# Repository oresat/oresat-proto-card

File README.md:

# "oresat-proto-card"

This is the "prototype" card for OreSat, meant to pioneer future cards and test the backplane, and be an 
easy way to hack in functionality. NOT MEANT FOR FLIGHT.

## Features

- Populates the two 1.27 mm connectors from the backplane.
- Populates all three SMPM RF connectors from the backplane.
- Standard TPS63070-bsaed buck/boost SPS (Vin = 2.5 to 7 V, Vout = 3.3V)
- Has our standard/favorite STM32F042K6 microcontroller.
   - With SWD, UART (FTDI), and CAN (to the backplane).
- Has lots of breakouts, but DO NOT POPULATE THE 0.1 IN CONNECTORS, THEY'RE TOO TALL!!!

## Connector information

- Main 1.27 mm connector ("Center" connector)
   - Samtec TFM-120-01-L-D-RA
   - https://www.digikey.com/products/en?lang=en&site=US&keywords=TFM-120-01-L-D-RA
   - Drawing: http://suddendocs.samtec.com/prints/tfm-1xx-xx-xxx-d-xxx-mkt.pdf
   - Brochure: http://suddendocs.samtec.com/catalog_english/tfm.pdf
   - 3D CAD: https://www.samtec.com/partnumber/tfm-120-01-l-d-ra?vendor=digikey#technical
   - Notes: the -RE1 model is better because of the solder stakes, but the female connector doesn't fit! The stakes get in the way :(

- Auxiliary 1.27 mm ("alt-left" connector)
   - Samtec TFM-110-01-L-D-RA

- RF (70 cm, L band, S band) conenctors
   - Card
      - Molex 73300-0030 (possible replacement is 73300-0020 but it has full detent that we don't want)
      - SMPM Connector Plug, Male Pin 50 Ohm Board Edge, Cutout; Surface Mount Solder, smooth bore
      - Molex w/3D: https://www.molex.com/molex/products/datasheet.jsp?part=active/0733000030_RF_COAX_CONNECTORS.xml
   - Barrell (connects card to backplane)
      - Molex 73300-0220 (alt but slightly different lengths: -0223, -0228)
      - SMPM female to female barrel adapter 
      - RF Adapters - In Series SMPM JACK/JACK BULLET .21IN
      - Molex w/3D: https://www.molex.com/molex/products/datasheet.jsp?part=active/0733000220_RF_COAX_CONNECTORS.xml

## LICENSE

Copyright Portland State Aerospace Society 2018.

This documentation describes Open Hardware and is licensed under the CERN OHL v. 1.2.

You may redistribute and modify this documentation under the terms of the CERN OHL v.1.2. [http://ohwr.org/cernohl](http://ohwr.org/cernohl). This documentation is distributed WITHOUT ANY EXPRESS OR IMPLIED WARRANTY, INCLUDING OF MERCHANTABILITY, SATISFACTORY QUALITY AND FITNESS FOR A PARTICULAR PURPOSE. Please see the CERN OHL v.1.2 for applicable conditions.

## Version Information

Version | Date       | Notes
--------|------------|-------------------------
3.0     | 2018/11/22 | Big changes in structure, mostly springs. Changed RF connectors to SMPM. Optimized layout for more proto area. 
2.0     | 2018/03/?? | New 1.27 mm connectors, again.
1.0     | ??         | New connectors.

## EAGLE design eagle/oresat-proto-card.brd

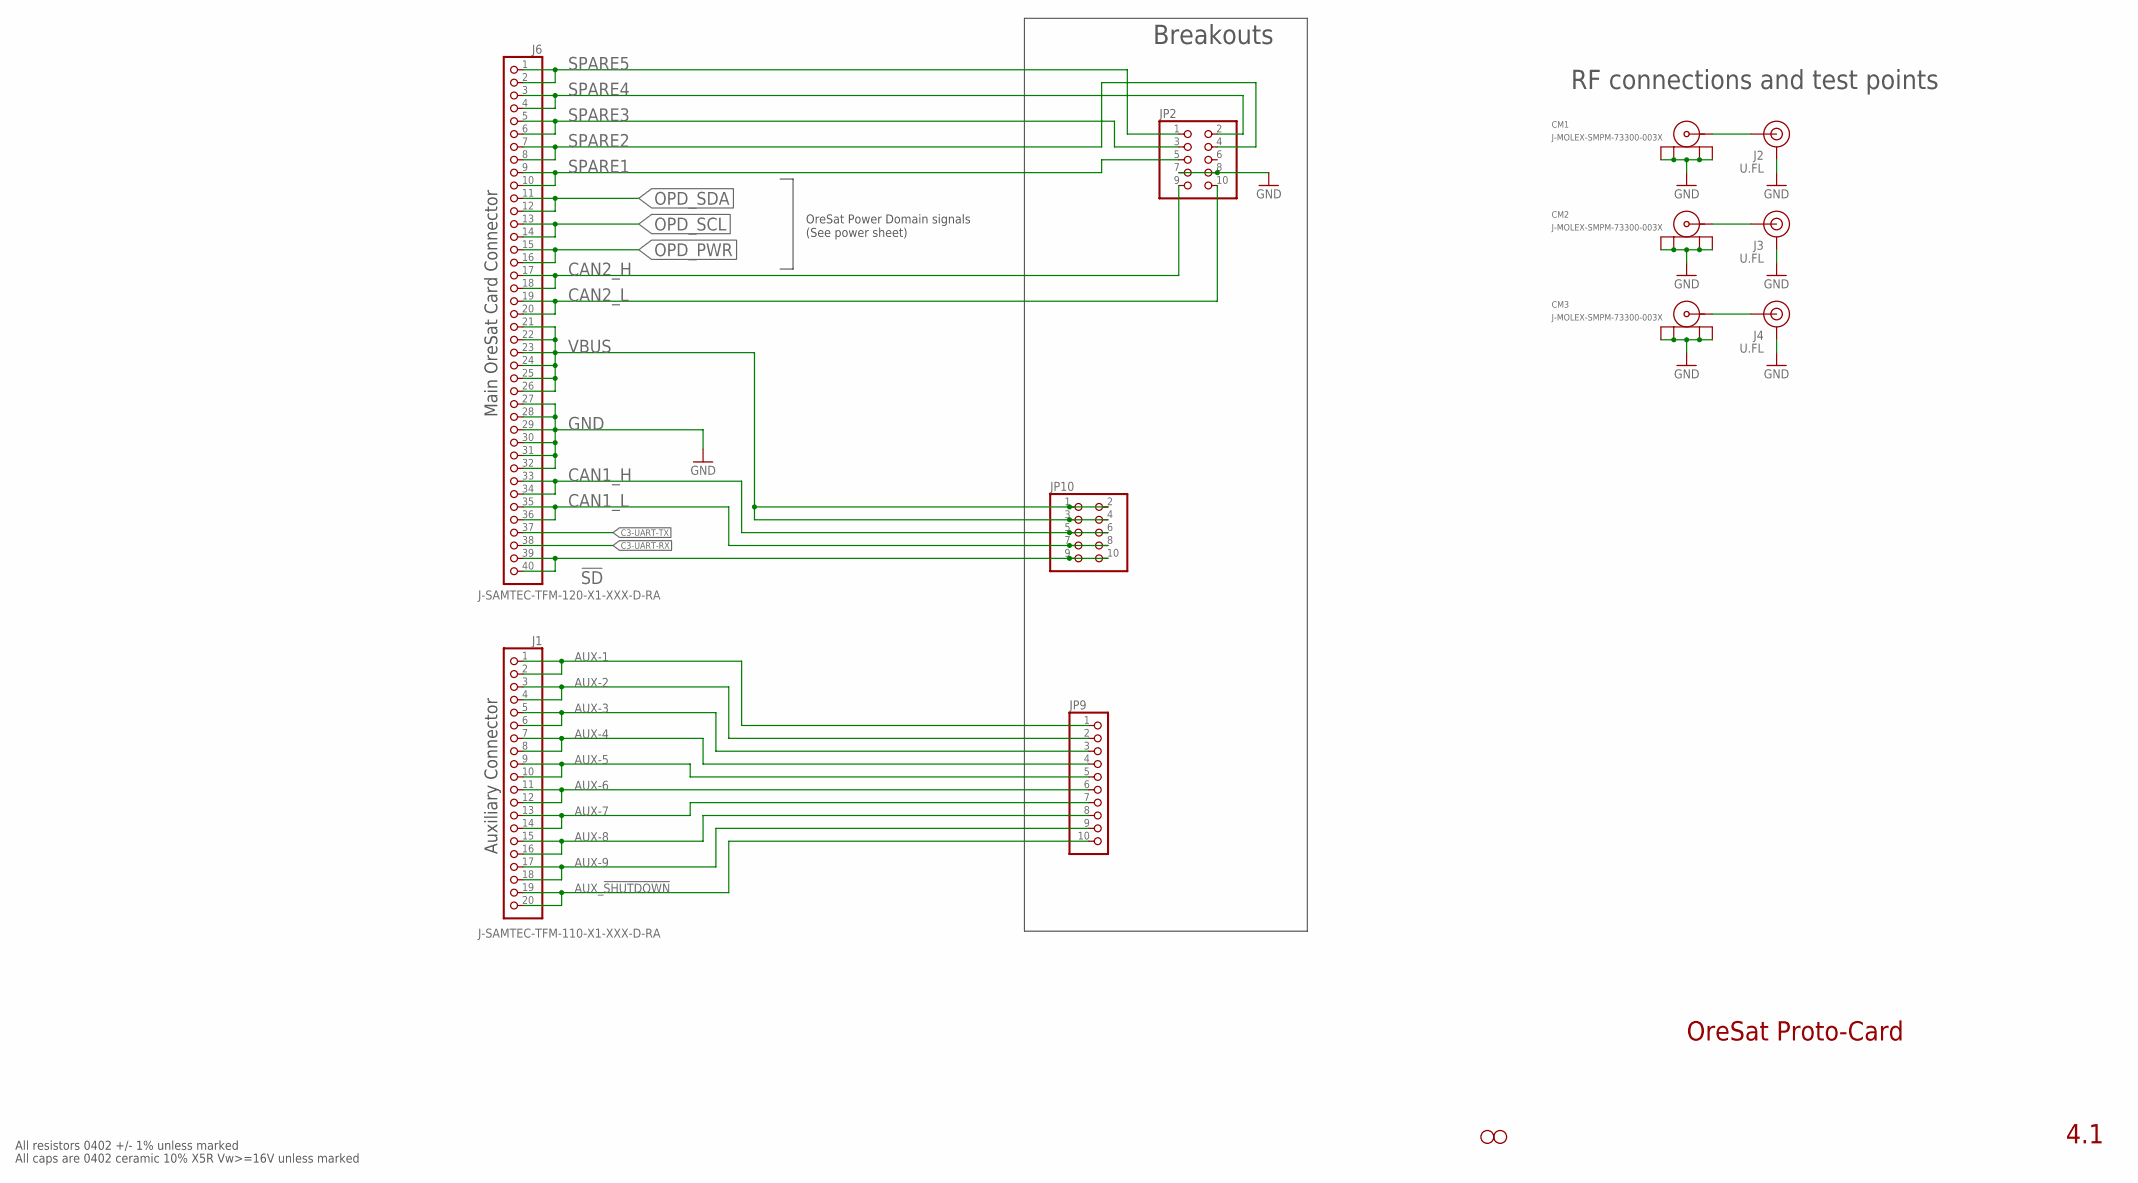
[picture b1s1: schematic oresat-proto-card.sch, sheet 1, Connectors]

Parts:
CM1, CM2, CM3: J-MOLEX-SMPM-73300-003X; J-MOLEX-SMPM-073300-003X; MPN 73300-0020
H2, H3: STAND-OFFTIGHT; STAND-OFF-TIGHT
J1: J-SAMTEC-TFM-110-X1-XXX-D-RA; MPN TFM-110-01-L-D-RA
J2, J3, J4: U.FL; MPN 1909763-1
J6: J-SAMTEC-TFM-120-X1-XXX-D-RA; MPN TFM-120-01-L-D-RA
JP2, JP10: PINHD-2X5; 2X05; MPN 67997-410HLF
JP9: PINHD-1X10; 1X10; MPN 61302011121

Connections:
!SD: J6.39, J6.40, JP10.9, JP10.10
AUX-1: J1.1, J1.2, JP9.1
AUX-2: J1.3, J1.4, JP9.2
AUX-3: J1.5, J1.6, JP9.3
AUX-4: J1.7, J1.8, JP9.4
AUX-5: J1.9, J1.10, JP9.5
AUX-6: J1.11, J1.12, JP9.6
AUX-7: J1.13, J1.14, JP9.7
AUX-8: J1.15, J1.16, JP9.8
AUX-9: J1.17, J1.18, JP9.9
AUX_!SHUTDOWN: J1.19, J1.20, JP9.10
C3-UART-RX: J6.38
C3-UART-TX: J6.37
CAN1_H: J6.33, J6.34, JP10.5, JP10.6
CAN1_L: J6.35, J6.36, JP10.7, JP10.8
CAN2_H: J6.17, J6.18, JP2.9; also elsewhere on the board
CAN2_L: J6.19, J6.20, JP2.10; also elsewhere on the board
GND: CM1.P$1 (SHIELD3), CM1.P$2 (SHIELD2), CM1.P$3 (SHIELD1), CM1.P$4 (SHIELD), CM2.P$1 (SHIELD3), CM2.P$2 (SHIELD2), CM2.P$3 (SHIELD1), CM2.P$4 (SHIELD), CM3.P$1 (SHIELD3), CM3.P$2 (SHIELD2), CM3.P$3 (SHIELD1), CM3.P$4 (SHIELD), J2.1 (GND), J2.2 (GND), J3.1 (GND), J3.2 (GND), J4.1 (GND), J4.2 (GND), J6.27, J6.28, J6.29, J6.30, J6.31, J6.32, JP2.7, JP2.8; also elsewhere on the board
unnamed: CM3.RF (CENTER), J4.FEED (SIGNAL)
OPD_PWR: J6.15, J6.16; also elsewhere on the board
OPD_SCL: J6.13, J6.14; also elsewhere on the board
OPD_SDA: J6.11, J6.12; also elsewhere on the board
RF1: CM1.RF (CENTER), J2.FEED (SIGNAL)
RF2: CM2.RF (CENTER), J3.FEED (SIGNAL)
SPARE1: J6.9, J6.10, JP2.5
SPARE2: J6.7, J6.8, JP2.4
SPARE3: J6.5, J6.6, JP2.3
SPARE4: J6.3, J6.4, JP2.2
SPARE5: J6.1, J6.2, JP2.1
VBUS: J6.21, J6.22, J6.23, J6.24, J6.25, J6.26, JP10.1, JP10.2, JP10.3, JP10.4; also elsewhere on the board

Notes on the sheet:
OreSat Proto-Card
4.1
All resistors 0402 +/- 1% unless marked
All caps are 0402 ceramic 10% X5R Vw>=16V unless marked
Auxiliary Connector
Main OreSat Card Connector
RF connections and test points
Breakouts
OreSat Power Domain signals (See power sheet)

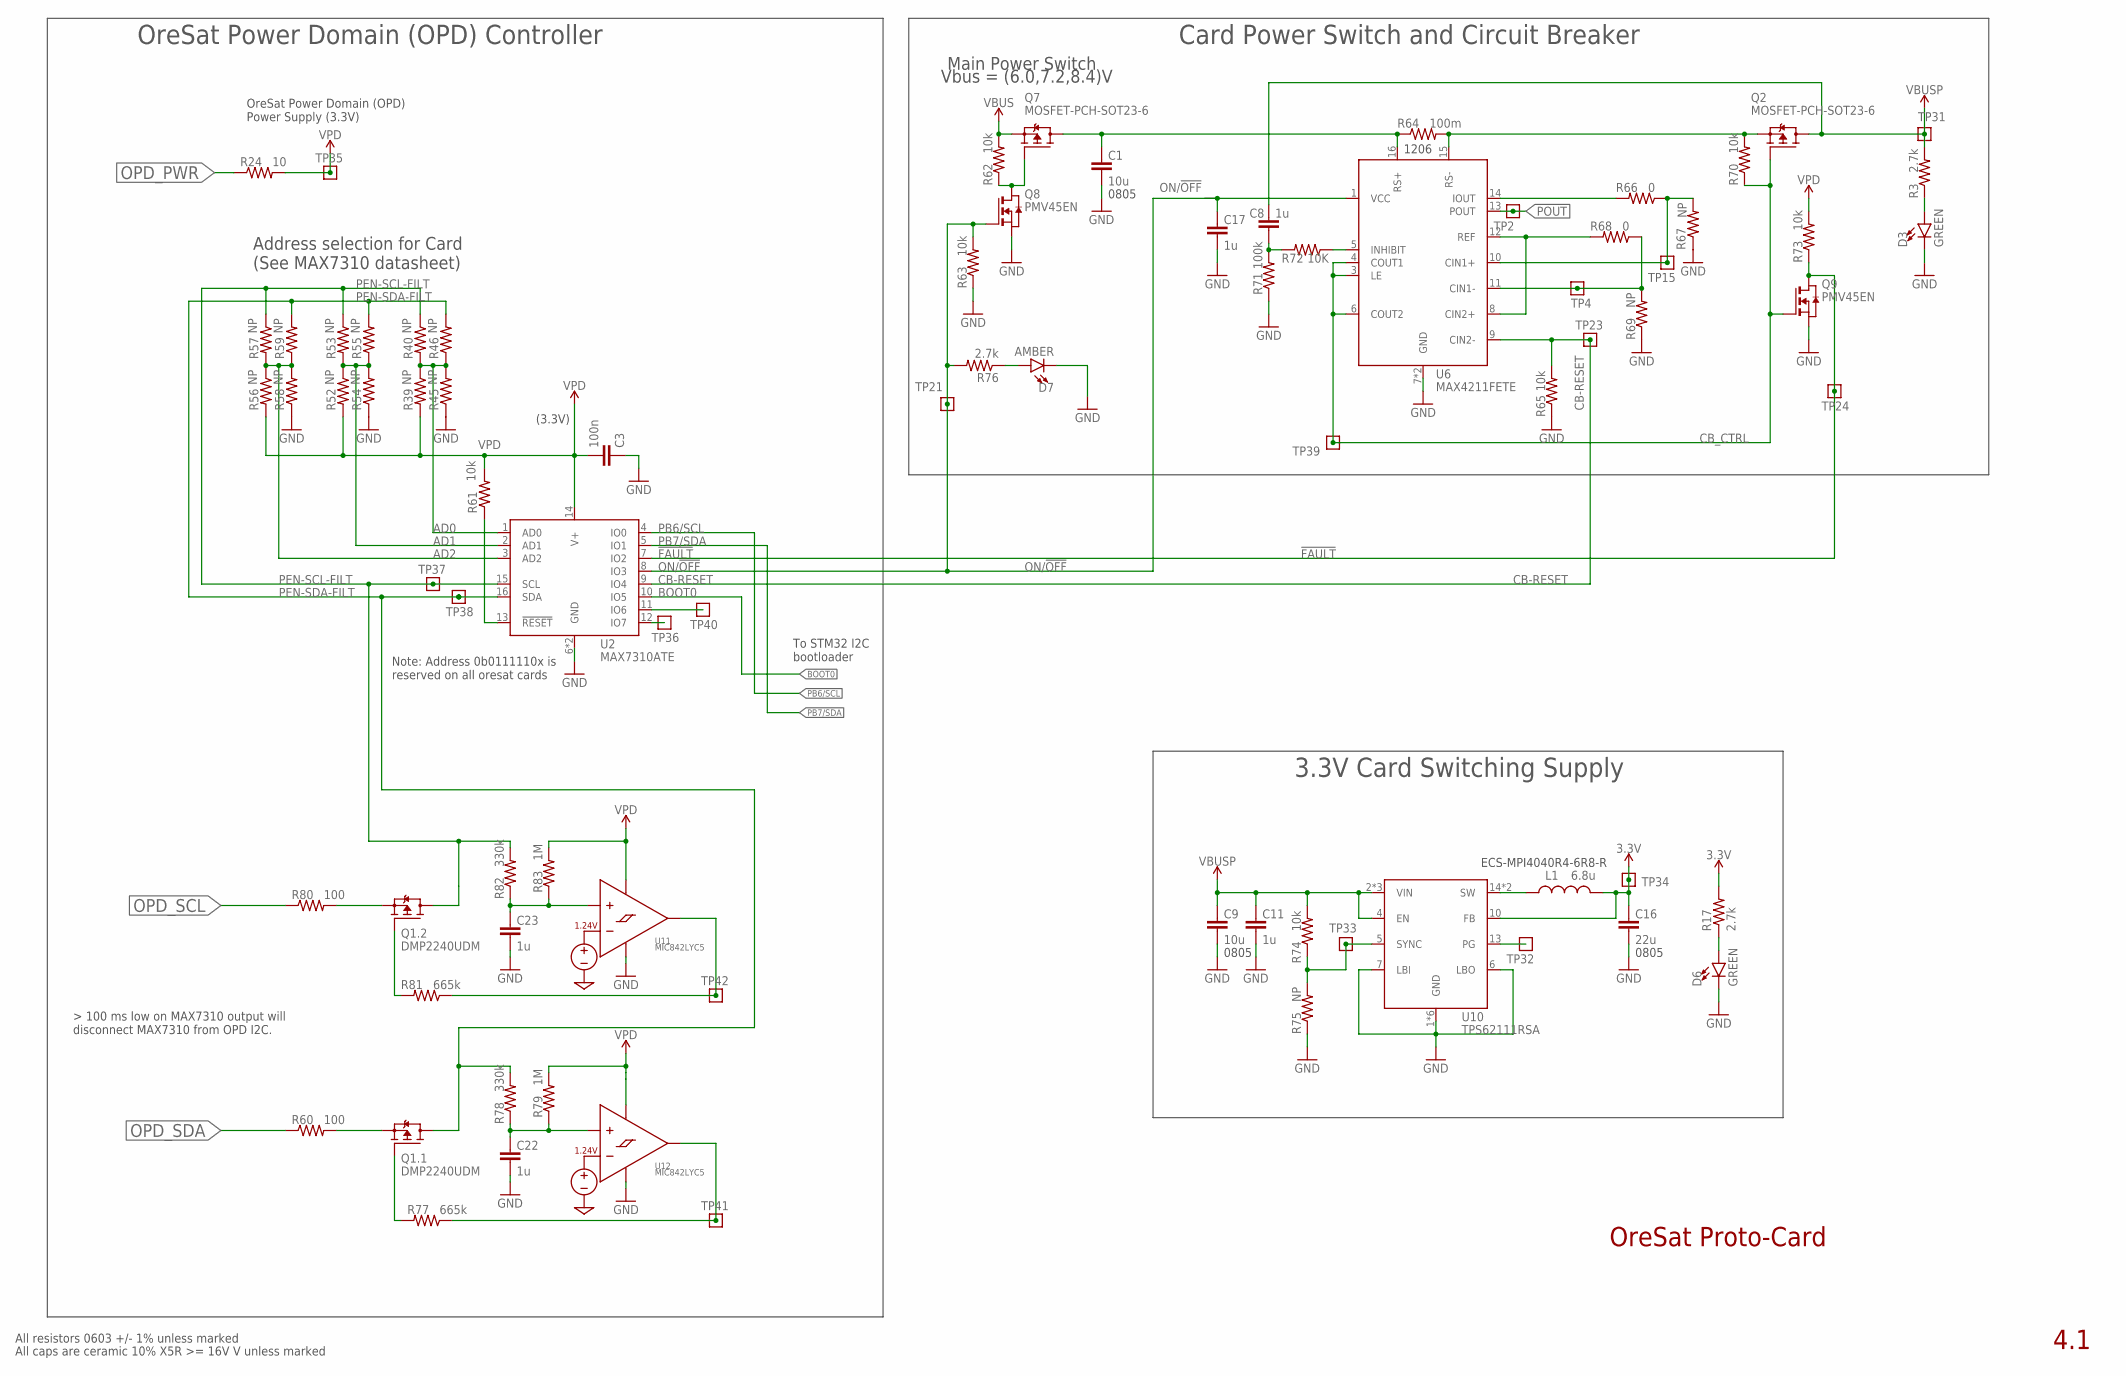
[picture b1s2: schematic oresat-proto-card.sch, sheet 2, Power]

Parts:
C1, C9: 10u; .0805-B-NOSILK; MPN CL21B106KOQNNNG
C3: 100n; .0603-C-NOSILK; MPN C0603C104K4PAC7867
C8: 1u; .0603-C-NOSILK
C11, C17, C22, C23: 1u; .0603-C-NOSILK; MPN CC0603KRX5R7BB105
C16: 22u; .0805-B-NOSILK; MPN GRM21BD71A226ME44L
D3, D6: GREEN; LED-0603; MPN SML-E12M8WT86
D7: AMBER; LED-0603; MPN IN-S63AT5A
L1: 6.8u; ECS-MPI4040; MPN ECS-MPI4040R4-6R8-R
Q1: DMP2240UDM; SOT23-6; MPN DMP2240UDM
Q2, Q7: MOSFET-PCH-SOT23-6; SOT23-6; MPN DMP3050LVT-7
Q8, Q9: PMV45EN; SOT23; MPN PMV45EN2R
R3, R17, R76: 2.7k; .0603-C-NOSILK; MPN ERA-3AEB272V
R24: 10; .0603-C-NOSILK; MPN RC0603FR-0710RL
R39, R40, R45, R46, R52, R53, R54, R55, R56, R57, R58, R59, R67, R69, R75: NP; .0603-C-NOSILK; MPN RC1005F6653CS
R60, R80: 100; .0603-C-NOSILK; MPN RC0603FR-07100RL
R61, R62, R63, R65, R70, R73, R74: 10k; .0603-C-NOSILK; MPN RNCP0603FTD10K0
R64: 100m; R1206; MPN CSR1206FTR100
R66, R68: 0; .0603-C-NOSILK; MPN RC0603JR-070RL
R71: 100k; .0603-C-NOSILK; MPN RC1005F6653CS
R72: 10K; .0603-C-NOSILK; MPN RC1005F6653CS
R77, R81: 665k; .0603-C-NOSILK; MPN RNCP0603FTD10K0
R78, R82: 330k; .0603-C-NOSILK; MPN CRGCQ0603F330K
R79, R83: 1M; .0603-C-NOSILK; MPN RC0603FR-071ML
TP2, TP4, TP15, TP21, TP23, TP24, TP31, TP32, TP33, TP34, TP35, TP36, TP37, TP38, TP39, TP40, TP41, TP42: TEST-POINT-LARGE-SQUARE; 1X01
U2: MAX7310ATE; QFN65P400X400X80-17T210; MPN MAX7310ATE
U6: MAX4211FETE; QFN65P400X400X80-17T210; MPN MAX4211FETE
U10: TPS62111RSA; S-PVQFN-16; MPN TPS62111RSA
U11, U12: MIC842LYC5; SC70-5

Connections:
3.3V: C16.1, L1.2, R17.2, TP34.1, U10.10 (FB); also elsewhere on the board
!FAULT: Q9.3 (D), R73.1, TP24.1, U2.7 (IO2)
AD0: R39.1, R40.2, R45.2, R46.1, U2.1 (AD0)
AD1: R52.1, R53.2, R54.2, R55.1, U2.2 (AD1)
AD2: R56.1, R57.2, R58.2, R59.1, U2.3 (AD2)
BOOT0: U2.10 (IO5); also elsewhere on the board
CB-RESET: R65.2, TP23.1, U2.9 (IO4), U6.9 (CIN2-)
CB_CTRL: Q2.3 (G), Q9.1 (G), R70.1, TP39.1, U6.3 (LE), U6.4 (COUT1), U6.6 (COUT2)
GND: C1.2, C3.1, C9.2, C11.2, C16.2, C17.2, C22.2, C23.2, D3.C, D6.C, D7.C, Q8.2 (S), Q9.2 (S), R45.1, R54.1, R58.1, R63.1, R65.1, R67.1, R69.1, R71.1, R75.1, U2.6 (GND), U2.EPAD (GND), U6.7 (GND), U6.EPAD (GND), U10.1 (GND), U10.6 (LBO), U10.7 (LBI), U10.9 (GND), U10.11 (GND), U10.12 (GND), U10.16 (GND), U10.PAD (GND), U11.2 (GND), U12.2 (GND); also elsewhere on the board
IOUT1: R66.2, U6.14 (IOUT)
unnamed: Q1.1 (G), R77.2
unnamed: Q1.3 (G), R81.2
unnamed: D3.A, R3.1
unnamed: D6.A, R17.1
unnamed: R61.1, U2.13 (!RESET)
unnamed: Q7.3 (G), Q8.3 (D), R62.1
unnamed: C1.1, Q7.1 (D), Q7.2 (D), Q7.5 (D), Q7.6 (D), R64.1, U6.16 (RS+)
unnamed: R66.1, R67.2, TP15.1, U6.10 (CIN1+)
unnamed: R68.1, R69.2, TP4.1, U6.11 (CIN1-)
unnamed: R68.2, U6.8 (CIN2+), U6.12 (REF)
unnamed: R72.1, U6.5 (INHIBIT)
unnamed: C8.1, R71.2, R72.2
unnamed: Q2.4 (S), R64.2, R70.2, U6.15 (RS-)
unnamed: D7.A, R76.1
unnamed: Q1.5 (S), R60.2
unnamed: R77.1, TP41.1, U12.4 (OUT)
unnamed: TP40.1, U2.11 (IO6)
unnamed: Q1.2 (S), R80.2
unnamed: R81.1, TP42.1, U11.4 (OUT)
unnamed: C23.1, R82.1, R83.1, U11.1 (INP)
unnamed: C22.1, R78.1, R79.1, U12.1 (INP)
unnamed: TP36.1, U2.12 (IO7)
ON/!OFF: C17.1, Q8.1 (G), R63.2, R76.2, TP21.1, U2.8 (IO3), U6.1 (VCC)
OPD_PWR: R24.1; also elsewhere on the board
OPD_SCL: R80.1; also elsewhere on the board
OPD_SDA: R60.1; also elsewhere on the board
PB6/SCL: U2.4 (IO0); also elsewhere on the board
PB7/SDA: U2.5 (IO1); also elsewhere on the board
PEN-SCL-FILT: Q1.4 (D), R40.1, R53.1, R57.1, R82.2, TP37.1, U2.15 (SCL)
PEN-SDA-FILT: Q1.6 (D), R46.2, R55.2, R59.2, R78.2, TP38.1, U2.16 (SDA)
POUT: TP2.1, U6.13 (POUT); also elsewhere on the board
TPS62111-PG1: TP32.1, U10.13 (PG)
TPS62111-SYNC1: R74.1, R75.2, TP33.1, U10.5 (SYNC)
TPS62111_SW3: L1.1, U10.14 (SW), U10.15 (SW)
VBUS: Q7.4 (S), R62.2; also elsewhere on the board
VBUSP: C8.2, C9.1, C11.1, Q2.1 (D), Q2.2 (D), Q2.5 (D), Q2.6 (D), R3.2, R74.2, TP31.1, U10.2 (VIN), U10.3 (VIN), U10.4 (EN), U10.8 (VIN); also elsewhere on the board
VPD: C3.2, R24.2, R39.2, R52.2, R56.2, R61.2, R73.2, R79.2, R83.2, TP35.1, U2.14 (V+), U11.5 (VDD), U12.5 (VDD)

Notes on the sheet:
4.1
Main Power Switch
Address selection for Card (See MAX7310 datasheet)
(3.3V)
0805
ECS-MPI4040R4-6R8-R
Vbus = (6.0,7.2,8.4)V
OreSat Power Domain (OPD) Power Supply (3.3V)
OreSat Power Domain (OPD) Controller
3.3V Card Switching Supply
Card Power Switch and Circuit Breaker
Note: Address 0b0111110x is reserved on all oresat cards
To STM32 I2C bootloader
1206
All resistors 0603 +/- 1% unless marked
All caps are ceramic 10% X5R >= 16V V unless marked
OreSat Proto-Card

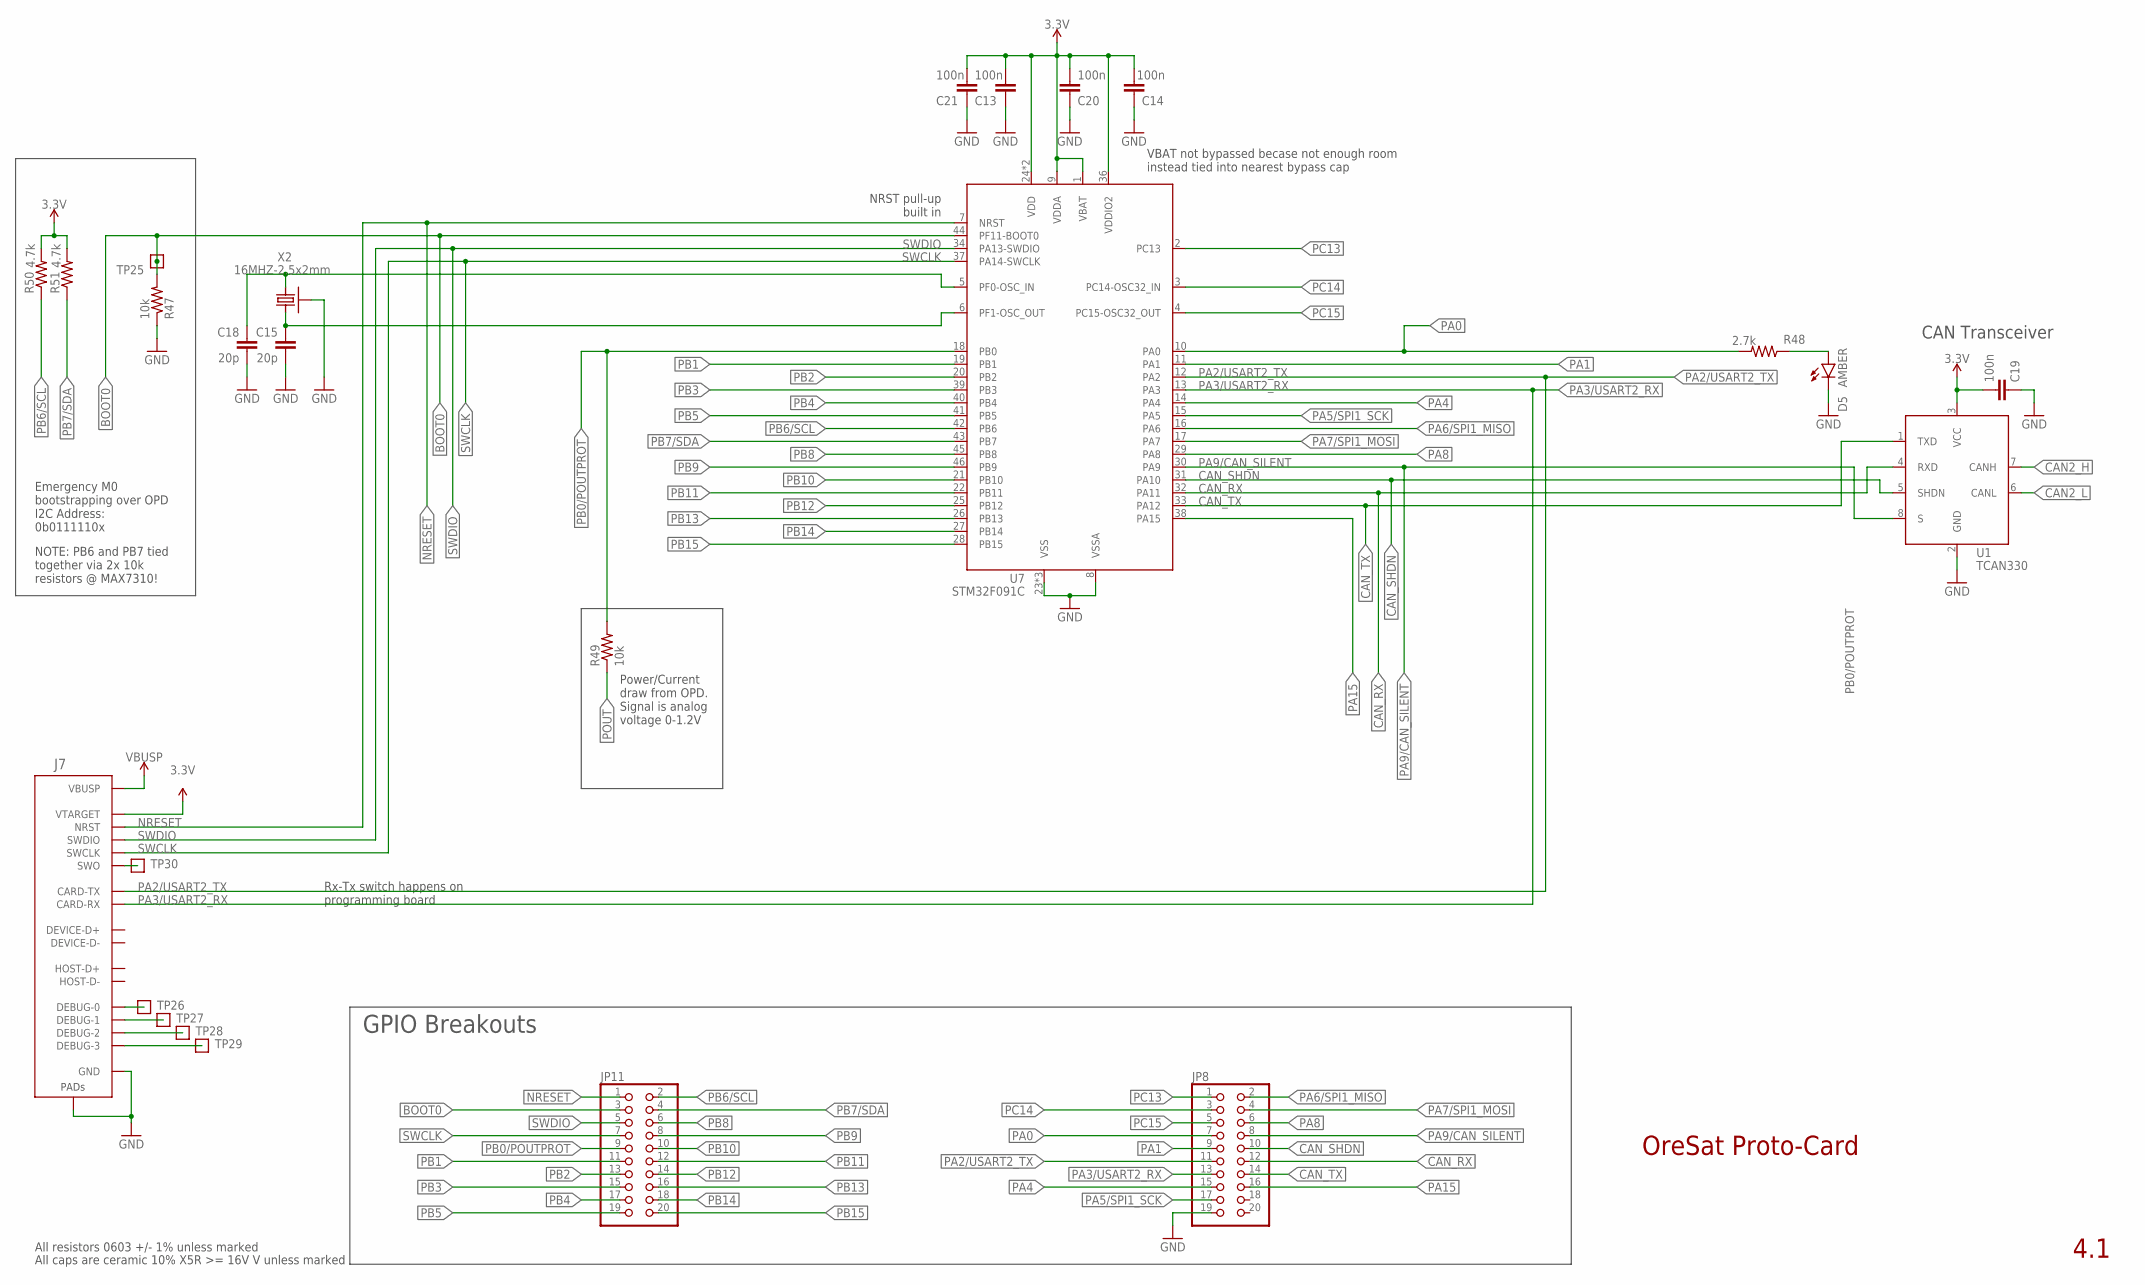
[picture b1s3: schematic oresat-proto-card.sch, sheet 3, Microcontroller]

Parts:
C13, C14, C19, C20, C21: 100n; .0603-C-NOSILK; MPN CL05B104KO5NNNC
C15, C18: 20p; .0603-C-NOSILK; MPN CL05C200JB51PNC
D5: AMBER; LED-0603; MPN IN-S63AT5A
J7: ORESAT-DEBUG-CONNECTOR-ALL; TE_2-1734592-0
JP8, JP11: PINHD-2X10; 2X10; MPN 67996-420HLF
R47, R49: 10k; .0603-C-NOSILK; MPN RC0402FR-0710KL
R48: 2.7k; .0603-C-NOSILK; MPN CRGCQ0402F2K7
R50, R51: 4.7k; .0603-C-NOSILK; MPN CRGCQ0402F2K7
TP25, TP26, TP27, TP28, TP29, TP30: TEST-POINT-LARGE-SQUARE; 1X01
U1: TCAN330; SOT23-8_TI-DCN; MPN TCAN330GDCNT
U7: STM32F091C; MPN STM32F042K6T7
X2: 16MHZ-2.5x2mm; CRYSTAL_2.5X2; MPN ECS-160-10-36Q-ES-TR

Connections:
3.3V: C13.2, C14.2, C19.2, C20.2, C21.2, J7.11 (VTARGET), R50.2, R51.2, U1.3 (VCC), U7.1 (VBAT), U7.9 (VDDA), U7.24 (VDD), U7.36 (VDDIO2), U7.48 (VDD); also elsewhere on the board
BOOT0: JP11.3, R47.2, TP25.1, U7.44 (PF11-BOOT0); also elsewhere on the board
CAN2_H: U1.7 (CANH); also elsewhere on the board
CAN2_L: U1.6 (CANL); also elsewhere on the board
CAN_RX: JP8.12, U1.4 (RXD), U7.32 (PA11)
CAN_SHDN: JP8.10, U1.5 (SHDN), U7.31 (PA10)
CAN_TX: JP8.14, U1.1 (TXD), U7.33 (PA12)
CRYSTALIN1: C18.1, U7.5 (PF0-OSC_IN), X2.1
CRYSTALOUT1: C15.1, U7.6 (PF1-OSC_OUT), X2.3 (2)
GND: C13.1, C14.1, C15.2, C18.2, C19.1, C20.1, C21.1, D5.C, J7.3 (GND), J7.6 (GND), J7.9 (GND), J7.PAD1 (PAD), J7.PAD2 (PAD), JP8.19, R47.1, U1.2 (GND), U7.8 (VSSA), U7.23 (VSS), U7.35 (VSS), U7.47 (VSS), X2.2 (SHIELD), X2.4 (SHIELD); also elsewhere on the board
unnamed: D5.A, R48.1
unnamed: J7.20 (DEBUG-3), TP29.1
unnamed: J7.19 (DEBUG-2), TP28.1
unnamed: J7.18 (DEBUG-1), TP27.1
unnamed: J7.17 (DEBUG-0), TP26.1
unnamed: J7.16 (SWO), TP30.1
NRESET: J7.10 (NRST), JP11.1, U7.7 (NRST)
PA0: JP8.7, R48.2, U7.10 (PA0)
PA1: JP8.9, U7.11 (PA1)
PA2/USART2_TX: J7.13 (CARD-TX), JP8.11, U7.12 (PA2)
PA3/USART2_RX: J7.12 (CARD-RX), JP8.13, U7.13 (PA3)
PA4: JP8.15, U7.14 (PA4)
PA5/SPI1_SCK: JP8.17, U7.15 (PA5)
PA6/SPI1_MISO: JP8.2, U7.16 (PA6)
PA7/SPI1_MOSI: JP8.4, U7.17 (PA7)
PA8: JP8.6, U7.29 (PA8)
PA9/CAN_SILENT: JP8.8, U1.8 (S), U7.30 (PA9)
PA15: JP8.16, U7.38 (PA15)
PB0/POUTPROT: JP11.9, R49.2, U7.18 (PB0)
PB1: JP11.11, U7.19 (PB1)
PB2: JP11.13, U7.20 (PB2)
PB3: JP11.15, U7.39 (PB3)
PB4: JP11.17, U7.40 (PB4)
PB5: JP11.19, U7.41 (PB5)
PB6/SCL: JP11.2, R50.1, U7.42 (PB6); also elsewhere on the board
PB7/SDA: JP11.4, R51.1, U7.43 (PB7); also elsewhere on the board
PB8: JP11.6, U7.45 (PB8)
PB9: JP11.8, U7.46 (PB9)
PB10: JP11.10, U7.21 (PB10)
PB11: JP11.12, U7.22 (PB11)
PB12: JP11.14, U7.25 (PB12)
PB13: JP11.16, U7.26 (PB13)
PB14: JP11.18, U7.27 (PB14)
PB15: JP11.20, U7.28 (PB15)
PC13: JP8.1, U7.2 (PC13)
PC14: JP8.3, U7.3 (PC14-OSC32_IN)
PC15: JP8.5, U7.4 (PC15-OSC32_OUT)
POUT: R49.1; also elsewhere on the board
SWCLK: J7.15 (SWCLK), JP11.7, U7.37 (PA14-SWCLK)
SWDIO: J7.14 (SWDIO), JP11.5, U7.34 (PA13-SWDIO)
VBUSP: J7.1 (VBUSP), J7.2 (VBUSP); also elsewhere on the board

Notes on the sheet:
NRST pull-up built in
CAN Transceiver
4.1
Emergency M0 bootstrapping over OPD I2C Address: 0b0111110x
NOTE: PB6 and PB7 tied together via 2x 10k resistors @ MAX7310!
Power/Current draw from OPD. Signal is analog voltage 0-1.2V
VBAT not bypassed becase not enough room instead tied into nearest bypass cap
Rx-Tx switch happens on programming board
GPIO Breakouts
All resistors 0603 +/- 1% unless marked
All caps are ceramic 10% X5R >= 16V V unless marked
OreSat Proto-Card

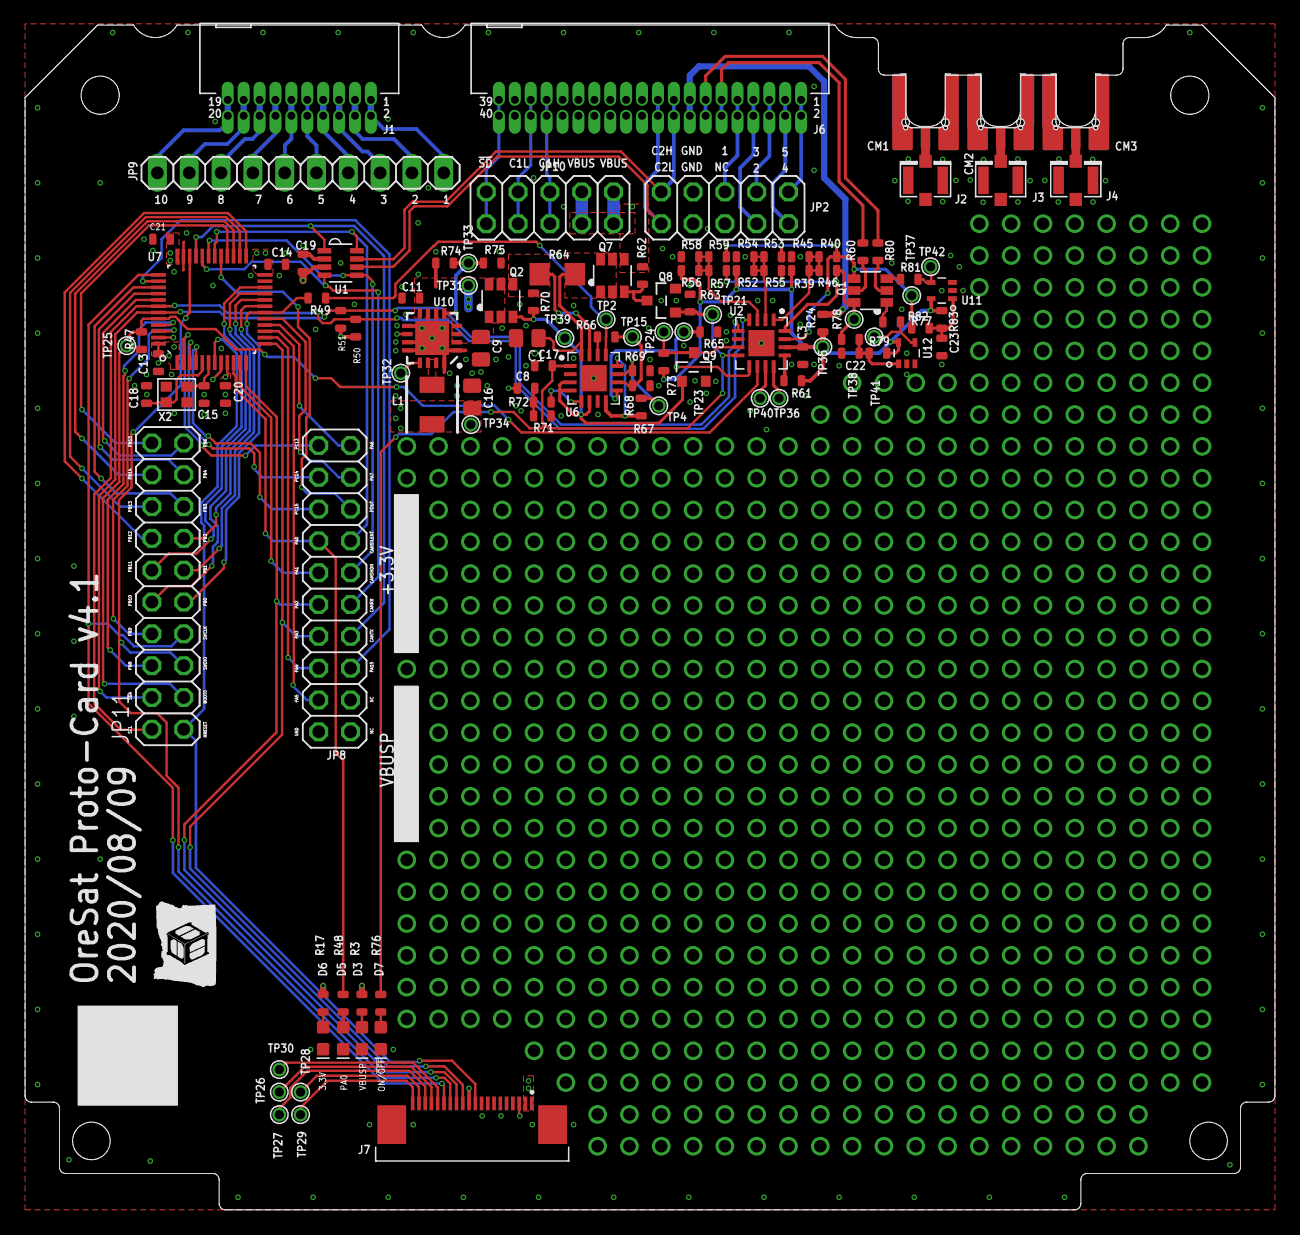
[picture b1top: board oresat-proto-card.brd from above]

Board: 4 copper layers, 99.8 x 94.6 mm, 119 parts (0 on the bottom side), 112 nets.

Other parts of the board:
U$1: ORESAT-CARD-V1.3-GENERIC-3RF

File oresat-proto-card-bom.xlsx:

Bill Of Materials for OreSat Prototype Card
source file: oresat-proto-card.sch
Last modified: 2020/01/07
PCB version: 4.0 |  |  | P/DNP = | Place/Do Not Place (DNP is for final production boards)
BOM revision: 1 |  |  | Generic = | Any generic part with the same characteristics are OK (e.g., bypass cap)
Cnt | Part References | P/DNP | Mfg | Mfg PN | Description | Generic | Dist | Dist Part Number
2 | R66, R68 | P | Yageo | RC0603JR-070RL | RES SMD 0 OHM JUMPER 1/10W 0603 | Y | Digi-Key | 311-0.0GRCT-ND
1 | R24 | P | Yageo | RC0603FR-0710RL | 10 Ohms ±1% 0.1W, 1/10W Chip Resistor 0603 | Y | Digi-Key | 311-10.0HRCT-ND
2 | R60, R80 | P | Yageo | RC0603FR-07100RL | 100 Ohms ±1% 0.1W, 1/10W Chip Resistor 0603 | Y | Digi-Key | 311-100HRCT-ND
1 | R64 | P | Stackpole | CSR1206FTR100 | 100 mOhms ±1% 0.5W, 1/2W Chip Resistor 1206 | Y | Digi-Key | CSR1206FTR100CT-ND
6 | C3, C13, C14, C19, C20, C21 | P | Samsung | CL05B104KO5NNNC | 0.1µF ±10% 16V Ceramic Capacitor X7R 0402 | Y | Digi-Key | 1276-1001-1-ND
11 | R61, R62, R63, R65, R70, R73, R77, R81, R47, R49, R74 | P | Stackpole | RNCP0603FTD10K0 | 10 kOhms ±1% 0.125W, 1/8W Chip Resistor 0603 | Y | Digi-Key | RNCP0603FTD10K0CT-ND
1 | C9 | P | Samsung | CL21B106KOQNNNG | 10µF ±10% 16V Ceramic Capacitor X7R 0805 | Y | Digi-Key | 1276-6472-1-ND
1 | X2 | P | ECS Inc. | ECS-160-10-36Q-ES-TR | 16MHz ±30ppm Crystal 10pF 80 Ohms | Y | Digi-Key | XC2181CT-ND
2 | R79, R83 | P | Yageo | RC0603FR-071ML | 1 MOhms ±1% 0.1W, 1/10W Chip Resistor 0603 | Y | Digi-Key | 311-1.00MHRCT-ND
4 | C11, C17, C22, C23 | P | Yageo | CC0603KRX5R7BB105 | 1µF ±10% 16V Ceramic Capacitor X5R 0603 | Y | Digi-Key | 311-1444-1-ND
6 | R3, R17, R48, R50, R51, R76 | P | Panasonic | ERA-3AEB272V | 2.7 kOhms ±0.1% 0.1W, 1/10W Chip Resistor 0603 | Y | Digi-Key | P2.7KDBCT-ND
2 | C15, C18 | P | Samsung | CL05C200JB51PNC | 20pF ±5% 50V Ceramic Capacitor C0G, NP0 0402 | Y | Digi-Key | 1276-6601-1-ND
1 | C16 | P | Murata | GRM21BD71A226ME44L | 22µF ±20% 10V Ceramic Capacitor X7T 0805 | Y | Digi-Key | 490-9959-1-ND
2 | R78, R82 | P | TE Connectivity | CRGCQ0603F330K | 330 kOhms ±1% 0.1W, 1/10W Chip Resistor 0603 | Y | Digi-Key | A129718CT-ND
1 | L1 | P | ECS | ECS-MPI4040R4-6R8-R | 6.8µH Shielded Inductor 2.4A 91mOhm | N | Digi-Key | XC2337CT-ND
2 | D5, D7 | P | Inolux | IN-S63AT5A | Amber 605nm LED Indication - Discrete 1.9V 0603 | Y | Digi-Key | 1830-1064-1-ND
1 | Q1 | P | Diodes Inc | DMP2240UDM | 2 P-Channel (Dual) 20V 2A 600mW Surface Mount SOT-26 | N | Digi-Key | DMP2240UDMDICT-ND
2 | D3, D6 | P | Rohm | SML-E12M8WT86 | Green 572nm LED Indication - Discrete 2.2V 0603 | Y | Digi-Key | 511-1584-1-ND
3 | CM1, CM2, CM3 | P | Molex | 73300-0020 | SMPM Connector Plug, Male Pin 50Ohm Board Edge | N | Digi-Key | WM10772-ND
1 | J1 | P | Samtec | TFM-110-01-L-D-RA | Connector Header Through Hole, Right Angle 20 position 0.050" | N | Digikey | SAM10113-ND
1 | J6 | P | Samtec | TFM-120-01-L-D-RA | Connector Header Through Hole, Right Angle 40 position 0.050" | N | Digi-Key | SAM10145-ND
1 | U6 | P | Maxim | MAX4211FETE | Current Monitor Regulator High-Side 16-TQFN | N | Digi-Key | MAX4211FETE+-ND
1 | U2 | P | Maxim | MAX7310ATE | I/O Expander 8 I²C, SMBus 400kHz 16-TQFN | N | Digi-Key | MAX7310ATE+-ND
2 | U11, U12 | P | Microchip | MIC842LYC5 | Comparator with Voltage Reference Push-Pull SC-70-5 | N | Digi-Key | 576-2927-1-ND
2 | Q2, Q7 | P | Diodes Inc | DMP3050LVT-7 | MOSFET-PCH-SOT23-6 | N | Digi-Key | DMP3050LVT-7DICT-ND
1 | C8 | NP |  |  | NP | Y
17 | R39, R40, R45, R46, R52, R53, R54, R55, R56, R57, R58, R59, R67, R69, R71, R72,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 | NP |  |  | NP | Y | Digi-Key | 1276-4275-1-ND
1 | J7 | P | Wurth |  | ORESAT-DEBUG-CONNECTOR-SOLAR | N
2 | Q8, Q9 | P | Nexperia | PMV45EN2R | N-Channel 30V 4.1A (Ta) 510mW (Ta), 5W (Tc) TO-236AB | N | Digi-Key | 1727-2307-1-ND
1 | U7 | P | STMicroelectronics | STM32F091CCT6TR | ARM® Cortex®-M0 STM32F0 Microcontroller | N | Digi-Key | 497-18749-1-ND
1 | U1 | P | Texas Instruments | TCAN330GDCNT | Transceiver CANbus SOT-23-8 | N | Digi-Key | 296-44211-1-ND
1 | U10 | P | Texas Instruments | TPS62111RSA | Buck Switching Regulator IC Positive Fixed 3.3V | N | Digi-Key | 296-37681-2-ND
3 | J2, J3, J4 | P | TE Connectivity | 1909763-1 | U.FL (UMCC) Connector Jack | N | Digi-Key | A118077CT-ND
VERSION INFO
 | Date | Notes
Rev
4.0r0 | 44013 | new BOM for version 4r0
3.3r1 | 17/12/2019 | Unfucked a lot of things (wrong part numbers, etc.)
3.3r0 | 43805 | new BOM for version 3.3r0
3.2r0 | 43681 | new BOM for version 3.2r0
3.1r0 | 43520 | new BOM for version 3.1r0
1.1r1 | ?? | Updated with actual orderable parts from Digi-Key
1.1r0 | ?? | Initial BOM. Not everything chosen, lots wrong. Mostly just exported from EAGLE.

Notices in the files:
parts and their libraries:
SparkFun-Connectors: Licensing: Creative Commons ShareAlike 4.0 International - https://creativecommons.org/licenses/by-sa/4.0
